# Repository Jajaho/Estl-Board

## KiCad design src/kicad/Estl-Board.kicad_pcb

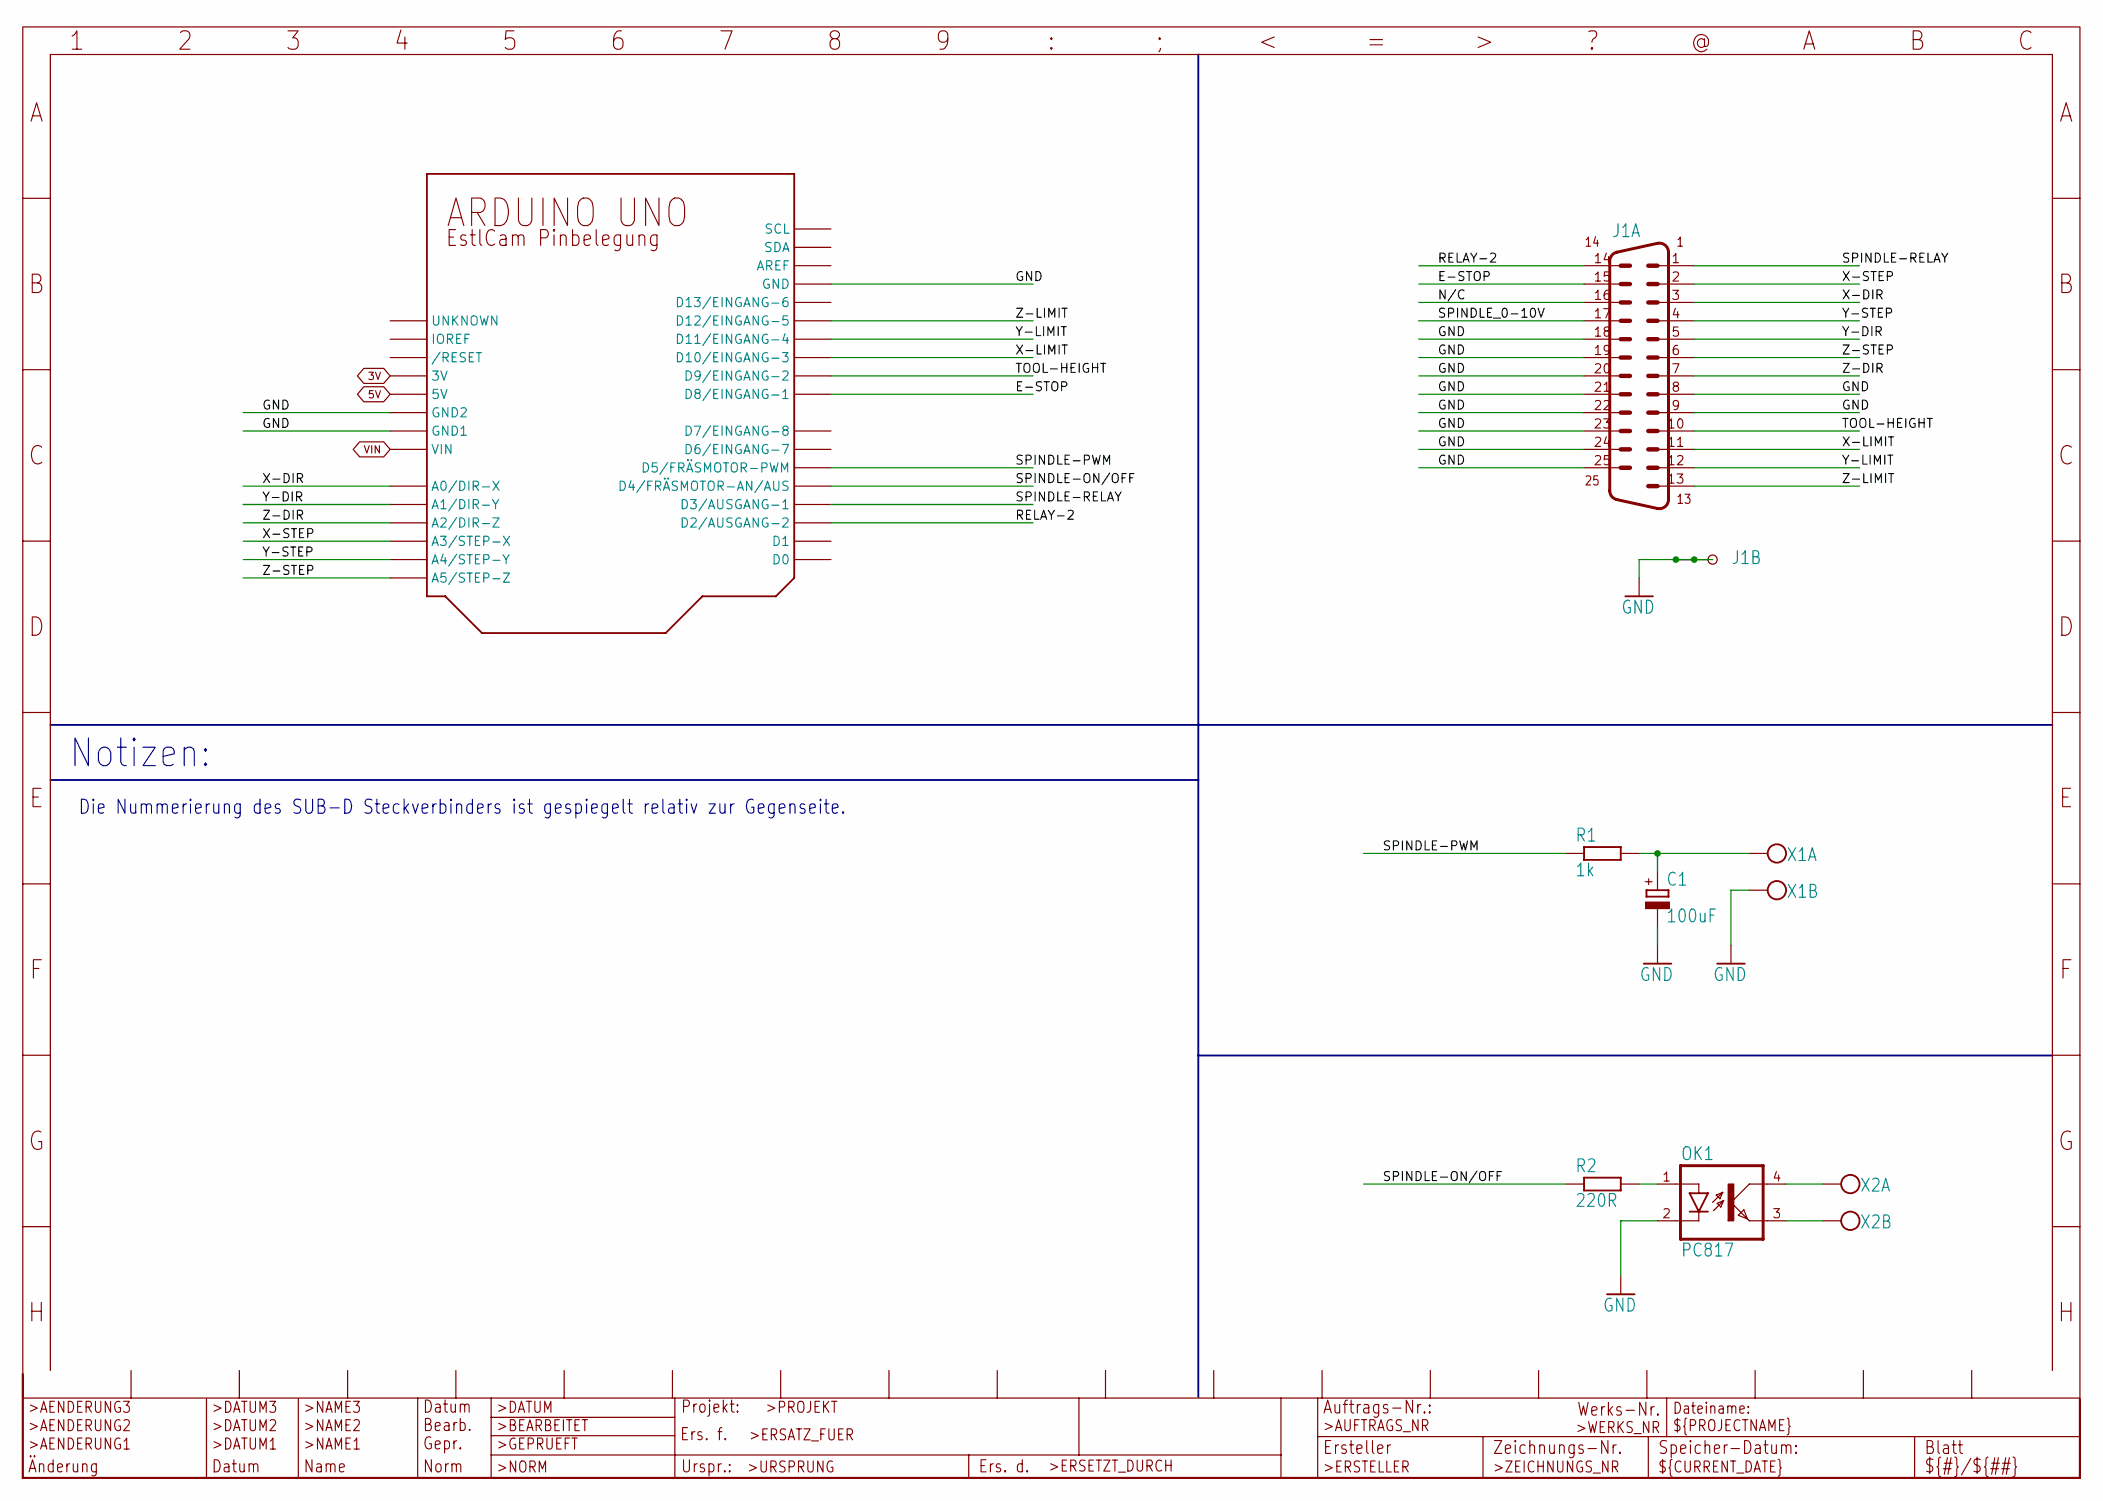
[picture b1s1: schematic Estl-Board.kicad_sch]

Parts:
C1: 100uF; E2-5-CAM
IC1: ARDUINO; ARDUINO_NOHOLES
J1: JP-316B; M25HP
OK1: PC817; DIP4
R1: 1k; 207_10+
R2: 220R; 207_10+
X1, X2: W237-102

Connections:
3V: IC1.3V
5V: IC1.5V
E-STOP: IC1.D8 (D8/EINGANG-1), J1.15 (E-STOP)
GND: C1.-, IC1.GND, IC1.GND1, IC1.GND2, J1.8 (A-STEP), J1.9 (A-DIR), J1.18 (GND0), J1.19 (GND1), J1.20 (GND2), J1.21 (GND3), J1.22 (GND4), J1.23 (GND5), J1.24 (GND6), J1.25 (GND7), J1.G1, J1.G2, OK1.2 (C), X1.2
unnamed: OK1.4 (COL), X2.1
unnamed: OK1.3 (EMIT), X2.2
unnamed: C1.+, R1.2, X1.1
unnamed: OK1.1 (A), R2.2
N/C: J1.16 (N/C)
RELAY-2: IC1.D2 (D2/AUSGANG-2), J1.14 (RELAY-2)
SPINDLE-ON/OFF: IC1.D4 (D4/FRÄSMOTOR-AN/AUS), R2.1
SPINDLE-PWM: IC1.D5 (D5/FRÄSMOTOR-PWM), R1.1
SPINDLE-RELAY: IC1.D3 (D3/AUSGANG-1), J1.1 (SPINDLE-RELAY)
SPINDLE_0-10V: J1.17 (SPINDLE_0-10V)
TOOL-HEIGHT: IC1.D9 (D9/EINGANG-2), J1.10 (TOOL-HEIGHT)
VIN: IC1.VIN
X-DIR: IC1.A0 (A0/DIR-X), J1.3 (X-DIR)
X-LIMIT: IC1.D10 (D10/EINGANG-3), J1.11 (X-LIMIT)
X-STEP: IC1.A3 (A3/STEP-X), J1.2 (X-STEP)
Y-DIR: IC1.A1 (A1/DIR-Y), J1.5 (Y-DIR)
Y-LIMIT: IC1.D11 (D11/EINGANG-4), J1.12 (Y-LIMIT)
Y-STEP: IC1.A4 (A4/STEP-Y), J1.4 (Y-STEP)
Z-DIR: IC1.A2 (A2/DIR-Z), J1.7 (Z-DIR)
Z-LIMIT: IC1.D12 (D12/EINGANG-5), J1.13 (Z-LIMIT)
Z-STEP: IC1.A5 (A5/STEP-Z), J1.6 (Z-STEP)

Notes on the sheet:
Notizen:
Die Nummerierung des SUB-D Steckverbinders ist gespiegelt relativ zur Gegenseite.

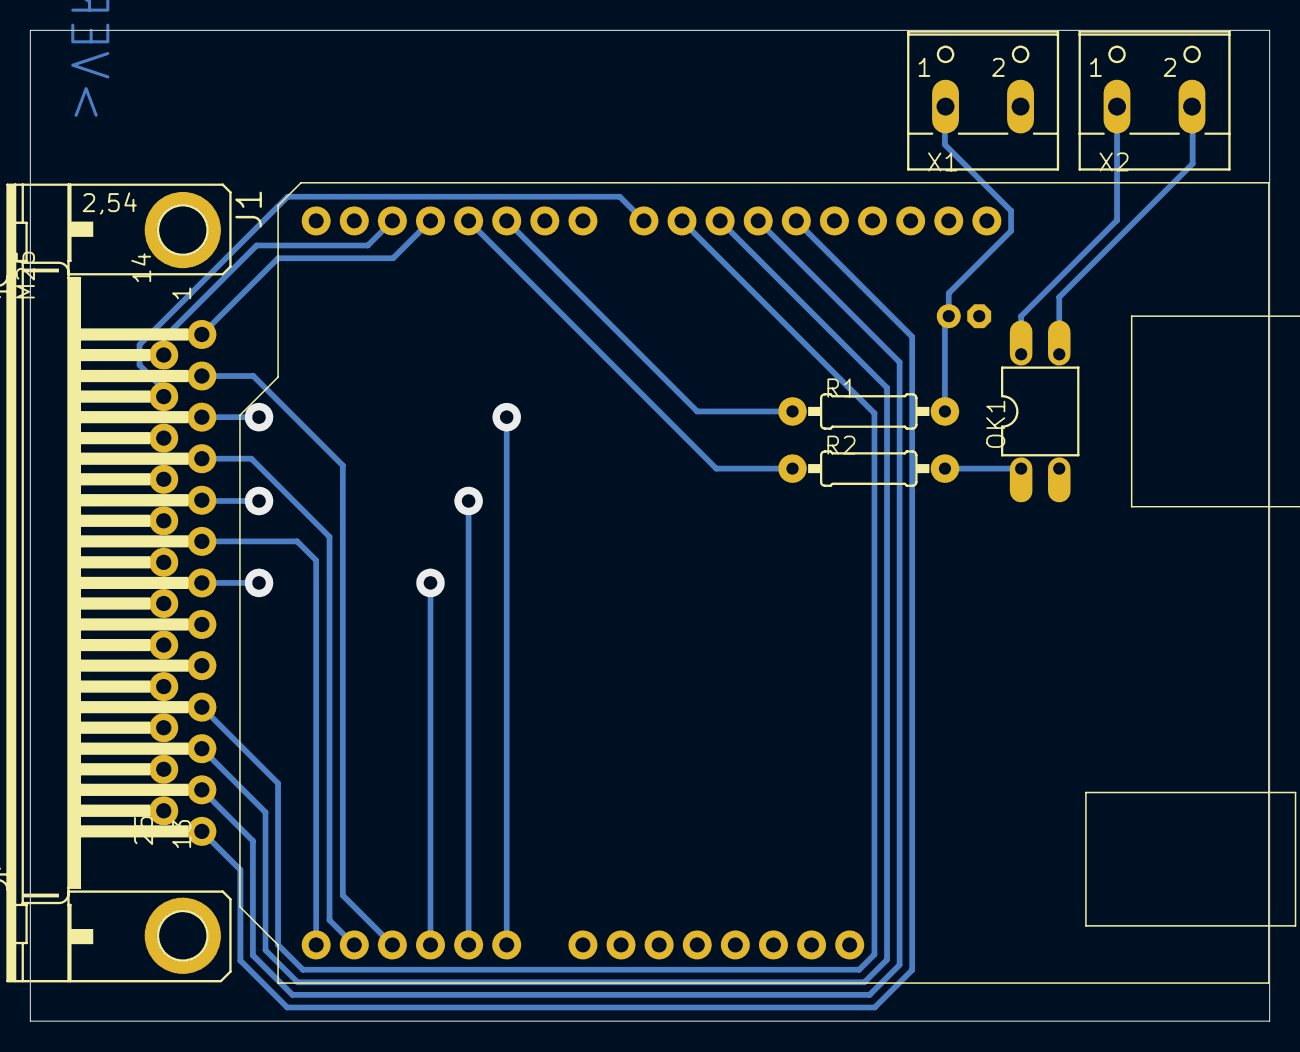
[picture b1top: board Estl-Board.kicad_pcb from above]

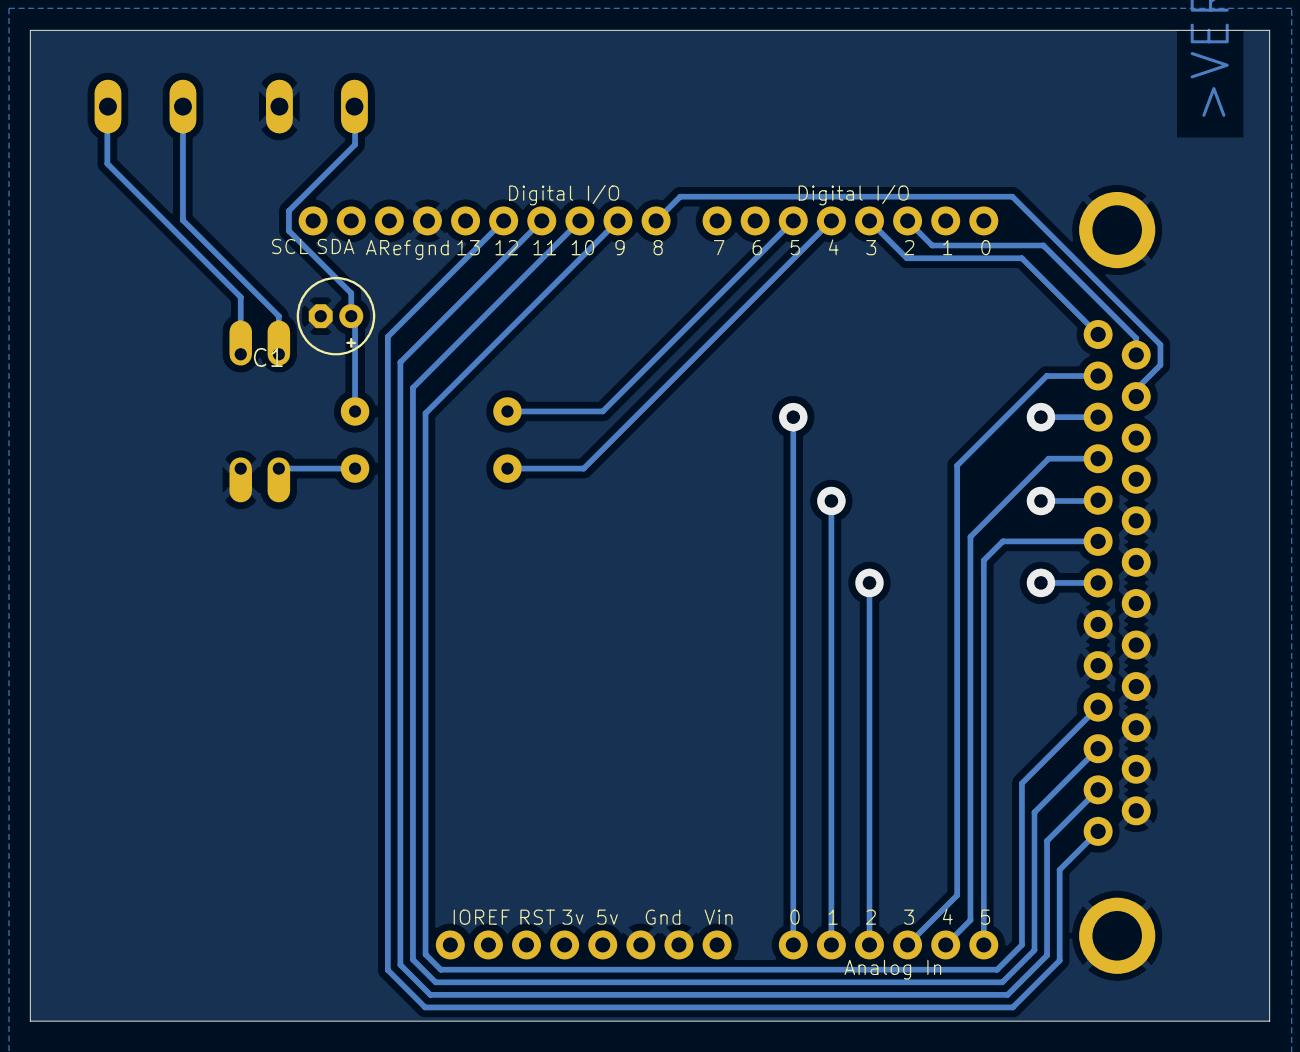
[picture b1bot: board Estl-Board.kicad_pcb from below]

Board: 2 copper layers, 82.6 x 66.0 mm, 8 parts (2 on the bottom side), 20 nets.

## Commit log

2023-07-22 Add src and cam files
